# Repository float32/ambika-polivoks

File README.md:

This work is a derivative of "[Voicecard-SVF-v05](https://github.com/pichenettes/ambika/tree/master/voicecard/hardware_design/pcb)" by [Emilie Gillet](https://github.com/pichenettes), used under [CC-BY-SA 3.0](https://creativecommons.org/licenses/by-sa/3.0/).
This work is licensed under [CC-BY-SA 3.0](https://creativecommons.org/licenses/by-sa/3.0/) by [Tyler Coy](https://github.com/float32).

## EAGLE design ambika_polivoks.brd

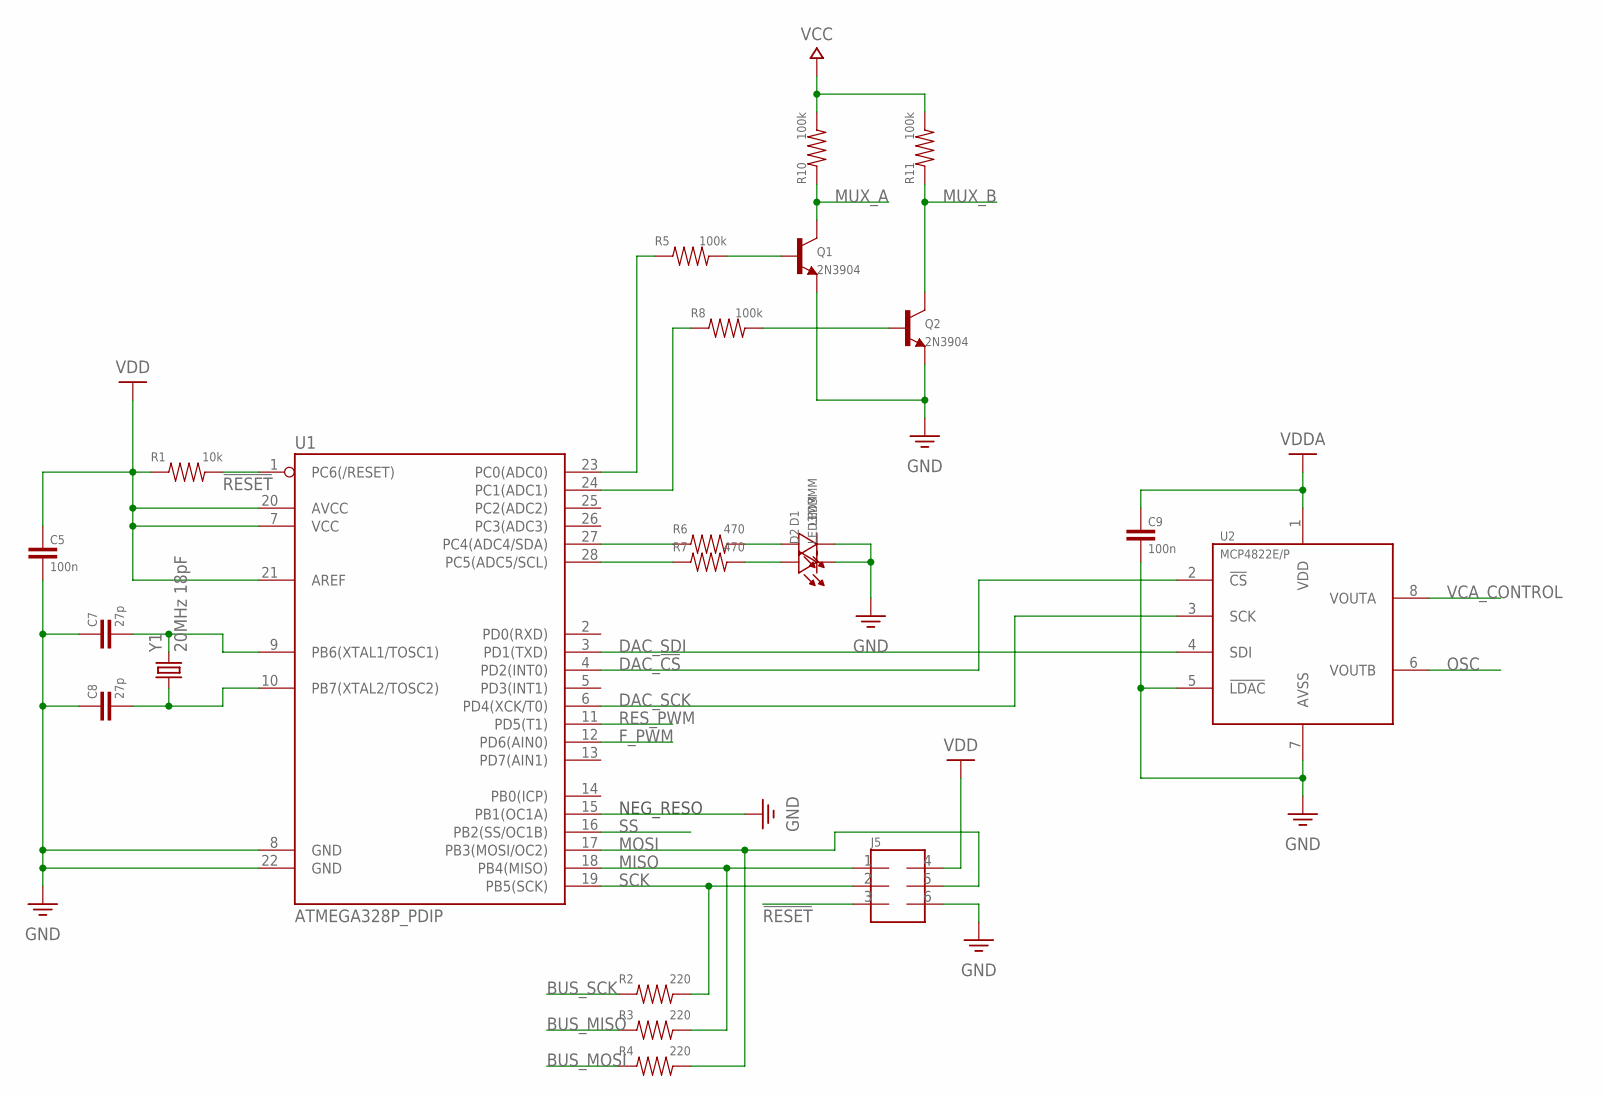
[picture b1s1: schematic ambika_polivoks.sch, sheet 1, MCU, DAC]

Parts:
C5, C9: 100n; CAP_0.1
C7, C8: 27p; CAP_0.1
D1, D2: LED3MM
J5: HEADER_2X3
Q1, Q2: 2N3904; TO-92_TRI
R1: 10k; RESISTOR_1/4W
R2, R3, R4: 220; RESISTOR_1/4W
R5, R8, R10, R11: 100k; RESISTOR_1/4W
R6, R7: 470; RESISTOR_1/4W
U1: ATMEGA328P_PDIP; DIP28
U2: MCP4822E/P; DIP8
Y1: 20MHz 18pF; HC49US

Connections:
!RESET: J5.3, R1.P$2 (2), U1.1 (PC6(/RESET))
BUS_MISO: R3.P$1 (1); also elsewhere on the board
BUS_MOSI: R4.P$1 (1); also elsewhere on the board
BUS_SCK: R2.P$1 (1); also elsewhere on the board
DAC_!CS: U1.4 (PD2(INT0)), U2.2 (!CS)
DAC_SCK: U1.6 (PD4(XCK/T0)), U2.3 (SCK)
DAC_SDI: U1.3 (PD1(TXD)), U2.4 (SDI)
F_PWM: U1.12 (PD6(AIN0)); also elsewhere on the board
GND: C5.2, C7.1, C8.1, C9.2, D1.K, D2.K, J5.6, Q1.1 (E), Q2.1 (E), U1.8 (GND), U1.15 (PB1(OC1A)), U1.22 (GND), U2.5 (!LDAC), U2.7 (AVSS); also elsewhere on the board
LED1: D2.A, R7.P$2 (2)
LED2: D1.A, R6.P$2 (2)
MISO: J5.1, R3.P$2 (2), U1.18 (PB4(MISO))
MOSI: J5.5, R4.P$2 (2), U1.17 (PB3(MOSI/OC2))
MUX_A: Q1.3 (C), R10.P$1 (1); also elsewhere on the board
MUX_B: Q2.3 (C), R11.P$1 (1); also elsewhere on the board
unnamed: C7.2, U1.9 (PB6(XTAL1/TOSC1)), Y1.2
unnamed: C8.2, U1.10 (PB7(XTAL2/TOSC2)), Y1.1
unnamed: Q1.2 (B), R5.P$2 (2)
unnamed: Q2.2 (B), R8.P$2 (2)
unnamed: R5.P$1 (1), U1.23 (PC0(ADC0))
unnamed: R8.P$1 (1), U1.24 (PC1(ADC1))
OSC: U2.6 (VOUTB); also elsewhere on the board
PC4: R6.P$1 (1), U1.27 (PC4(ADC4/SDA))
PC5: R7.P$1 (1), U1.28 (PC5(ADC5/SCL))
RES_PWM: U1.11 (PD5(T1)); also elsewhere on the board
SCK: J5.2, R2.P$2 (2), U1.19 (PB5(SCK))
SS: U1.16 (PB2(SS/OC1B)); also elsewhere on the board
VCA_CONTROL: U2.8 (VOUTA); also elsewhere on the board
VCC: R10.P$2 (2), R11.P$2 (2); also elsewhere on the board
VDD: C5.1, J5.4, R1.P$1 (1), U1.7 (VCC), U1.20 (AVCC), U1.21 (AREF); also elsewhere on the board
VDDA: C9.1, U2.1 (VDD); also elsewhere on the board

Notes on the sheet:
NEG_RESO

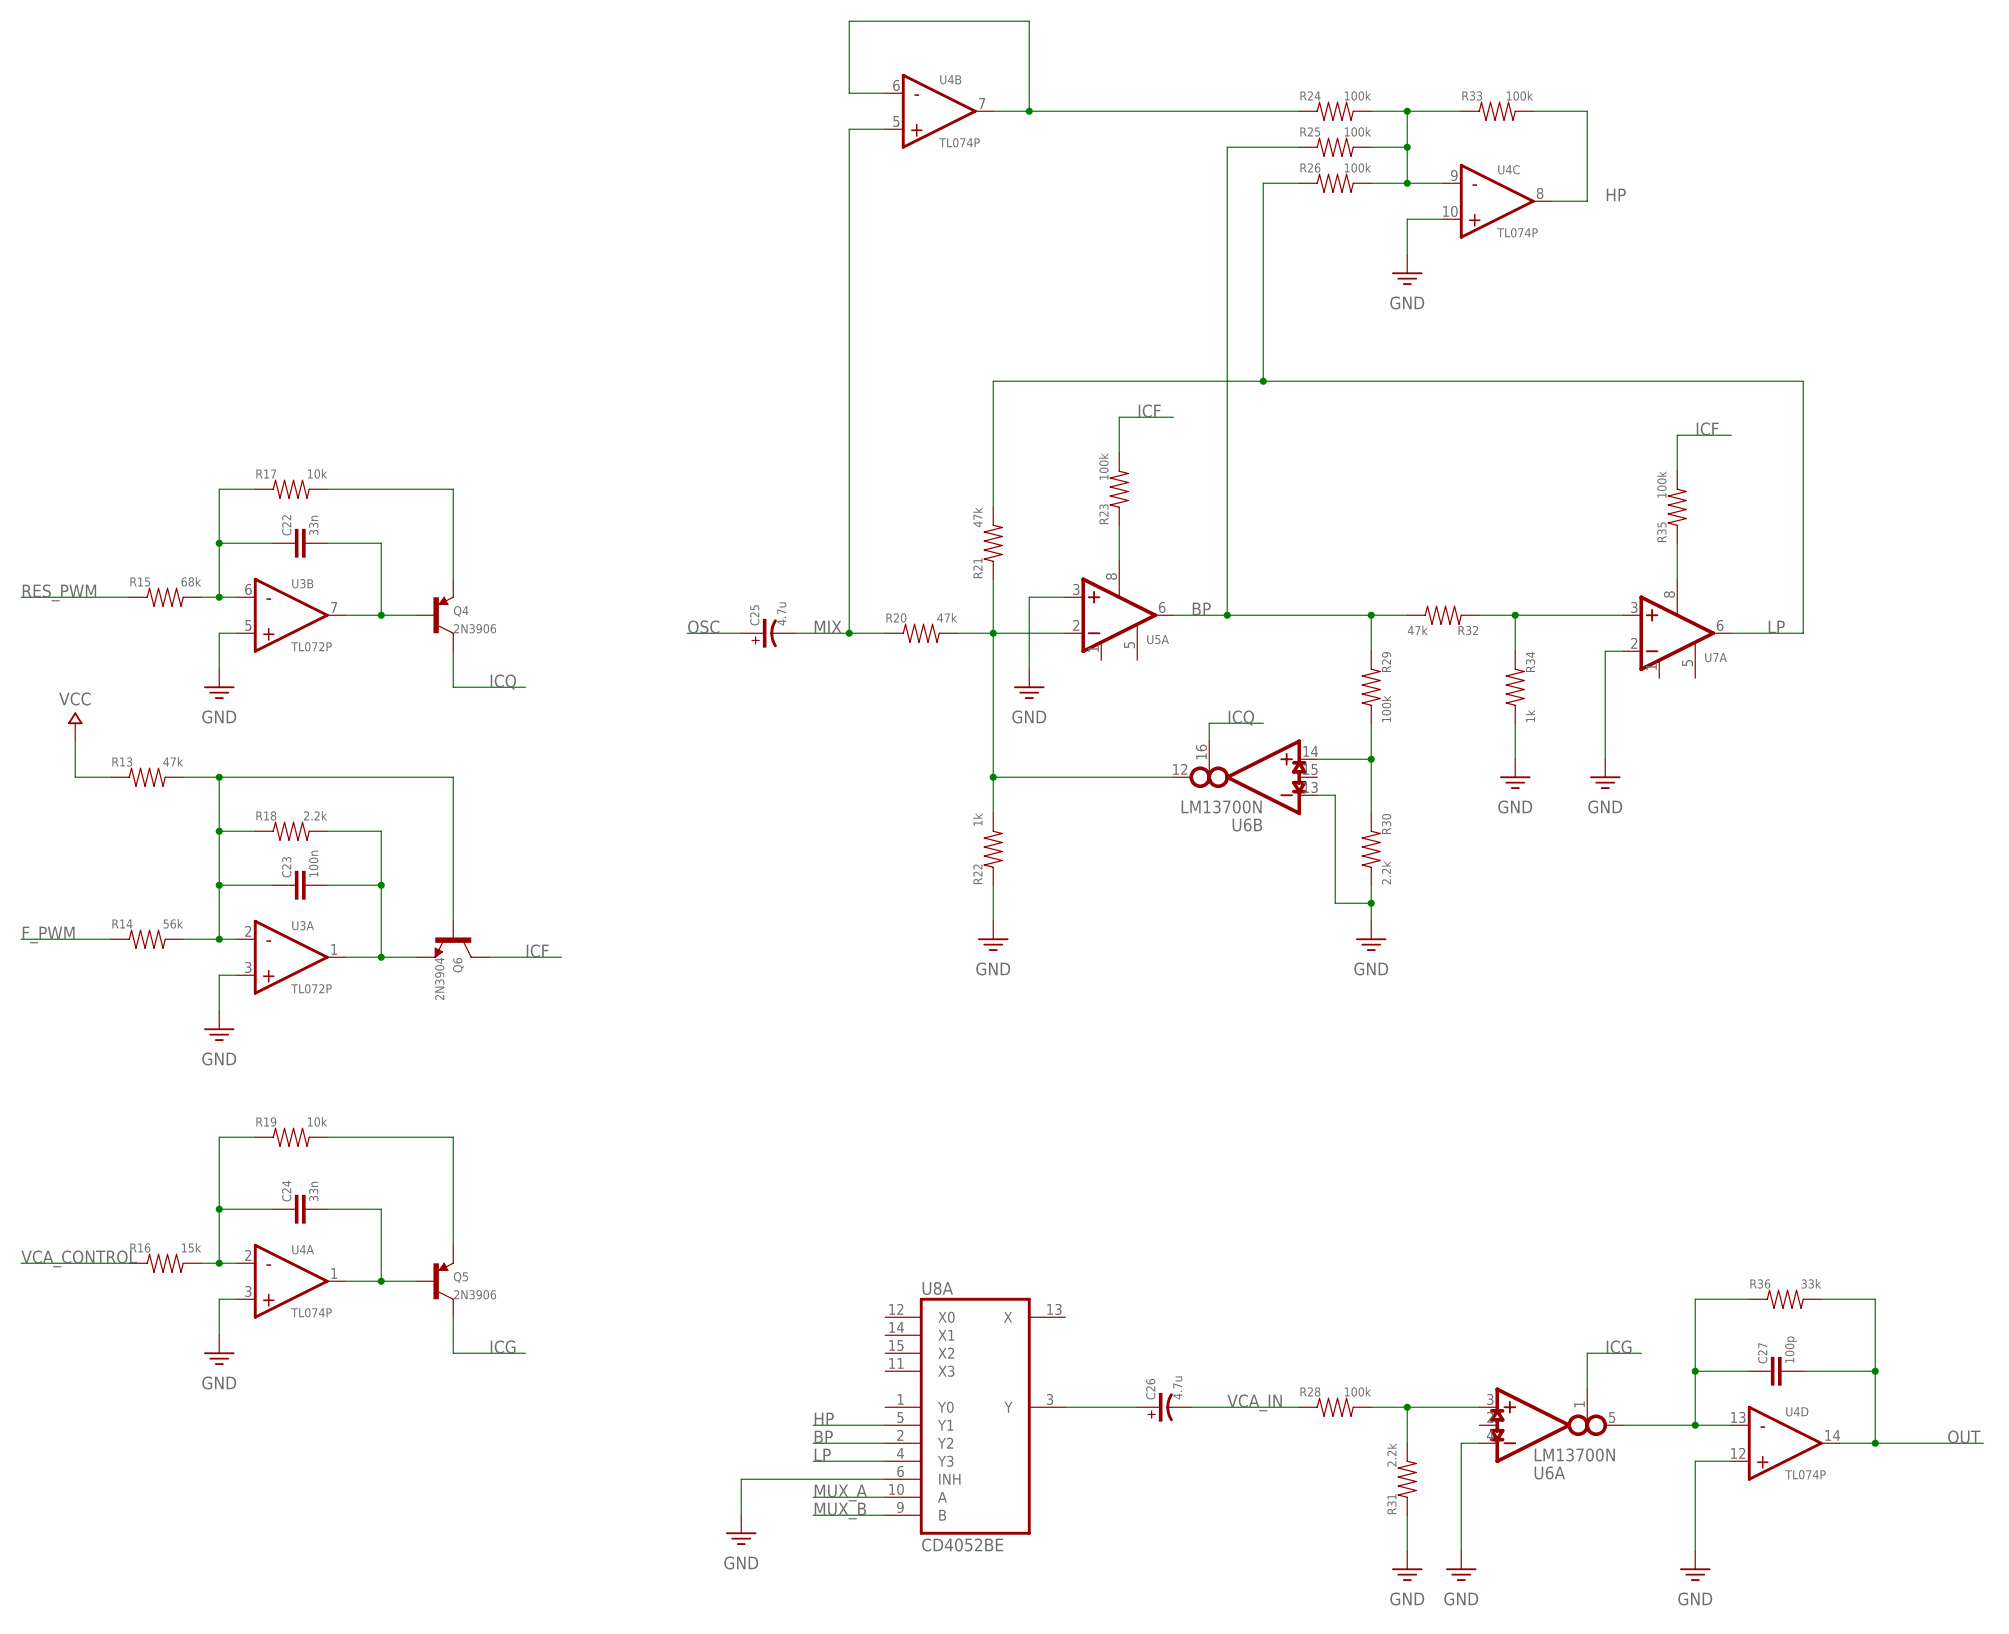
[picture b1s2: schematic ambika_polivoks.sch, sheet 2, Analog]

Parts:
C22, C24: 33n; CAP_0.1
C23: 100n; CAP_0.1
C25: 4.7u; CAP_ELEC_5MM_2MM_HORZ1
C26: 4.7u; CAP_ELEC_5MM_2MM_HORZ2
C27: 100p; CAP_0.1
Q4, Q5: 2N3906; TO-92_TRI
Q6: 2N3904; TO-92_TRI
R13, R20, R21, R32: 47k; RESISTOR_1/4W
R14: 56k; RESISTOR_1/4W
R15: 68k; RESISTOR_1/4W
R16: 15k; RESISTOR_1/4W
R17, R19: 10k; RESISTOR_1/4W
R18, R30, R31: 2.2k; RESISTOR_1/4W
R22, R34: 1k; RESISTOR_1/4W
R23, R24, R25, R26, R28, R29, R33, R35: 100k; RESISTOR_1/4W
R36: 33k; RESISTOR_1/4W
U3: TL072P; DIP8
U4: TL074P; DIP14
U5, U7: LM4250CN; DIP8
U6: LM13700N; DIP16
U8: CD4052BE; DIP16

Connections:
BP: R25.P$1 (1), R29.P$1 (1), R32.P$2 (2), U5.6 (OUTPUT), U8.2 (Y2)
F_PWM: R14.P$1 (1); also elsewhere on the board
GND: R22.P$1 (1), R30.P$2 (2), R31.P$1 (1), R34.P$2 (2), U3.3 (IN+), U3.5 (IN+), U4.3 (IN+), U4.10 (IN+), U4.12 (IN+), U5.3 (V+), U6.4 (-), U6.13 (-), U7.2 (V-), U8.6 (INH); also elsewhere on the board
HP: R33.P$2 (2), U4.8 (OUT), U8.5 (Y1)
ICF: Q6.3 (C), R23.P$2 (2), R35.P$2 (2)
ICG: Q5.3 (C), U6.1 (AMP_BIAS)
ICQ: Q4.3 (C), U6.16 (AMP_BIAS)
LP: R21.P$2 (2), R26.P$1 (1), U7.6 (OUTPUT), U8.4 (Y3)
MIX: C25.C, R20.P$1 (1), U4.5 (IN+)
MUX_A: U8.10 (A); also elsewhere on the board
MUX_B: U8.9 (B); also elsewhere on the board
unnamed: C26.A, U8.3 (Y)
unnamed: R24.P$1 (1), U4.6 (IN-), U4.7 (OUT)
unnamed: R24.P$2 (2), R25.P$2 (2), R26.P$2 (2), R33.P$1 (1), U4.9 (IN-)
unnamed: C23.2, Q6.1 (E), R18.P$2 (2), U3.1 (OUT)
unnamed: C22.2, Q4.2 (B), U3.7 (OUT)
unnamed: C22.1, R15.P$2 (2), R17.P$1 (1), U3.6 (IN-)
unnamed: Q4.1 (E), R17.P$2 (2)
unnamed: C23.1, Q6.2 (B), R13.P$2 (2), R14.P$2 (2), R18.P$1 (1), U3.2 (IN-)
unnamed: R20.P$2 (2), R21.P$1 (1), R22.P$2 (2), U5.2 (V-), U6.12 (OUTPUT)
unnamed: C24.1, R16.P$2 (2), R19.P$1 (1), U4.2 (IN-)
unnamed: C24.2, Q5.2 (B), U4.1 (OUT)
unnamed: Q5.1 (E), R19.P$2 (2)
unnamed: R23.P$1 (1), U5.8 (SET)
unnamed: R32.P$1 (1), R34.P$1 (1), U7.3 (V+)
unnamed: R29.P$2 (2), R30.P$1 (1), U6.14 (+)
unnamed: R28.P$2 (2), R31.P$2 (2), U6.3 (+)
unnamed: C27.1, R36.P$1 (1), U4.13 (IN-), U6.5 (OUTPUT)
unnamed: R35.P$1 (1), U7.8 (SET)
OSC: C25.A; also elsewhere on the board
OUT: C27.2, R36.P$2 (2), U4.14 (OUT); also elsewhere on the board
RES_PWM: R15.P$1 (1); also elsewhere on the board
VCA_CONTROL: R16.P$1 (1); also elsewhere on the board
VCA_IN: C26.C, R28.P$1 (1)
VCC: R13.P$1 (1); also elsewhere on the board

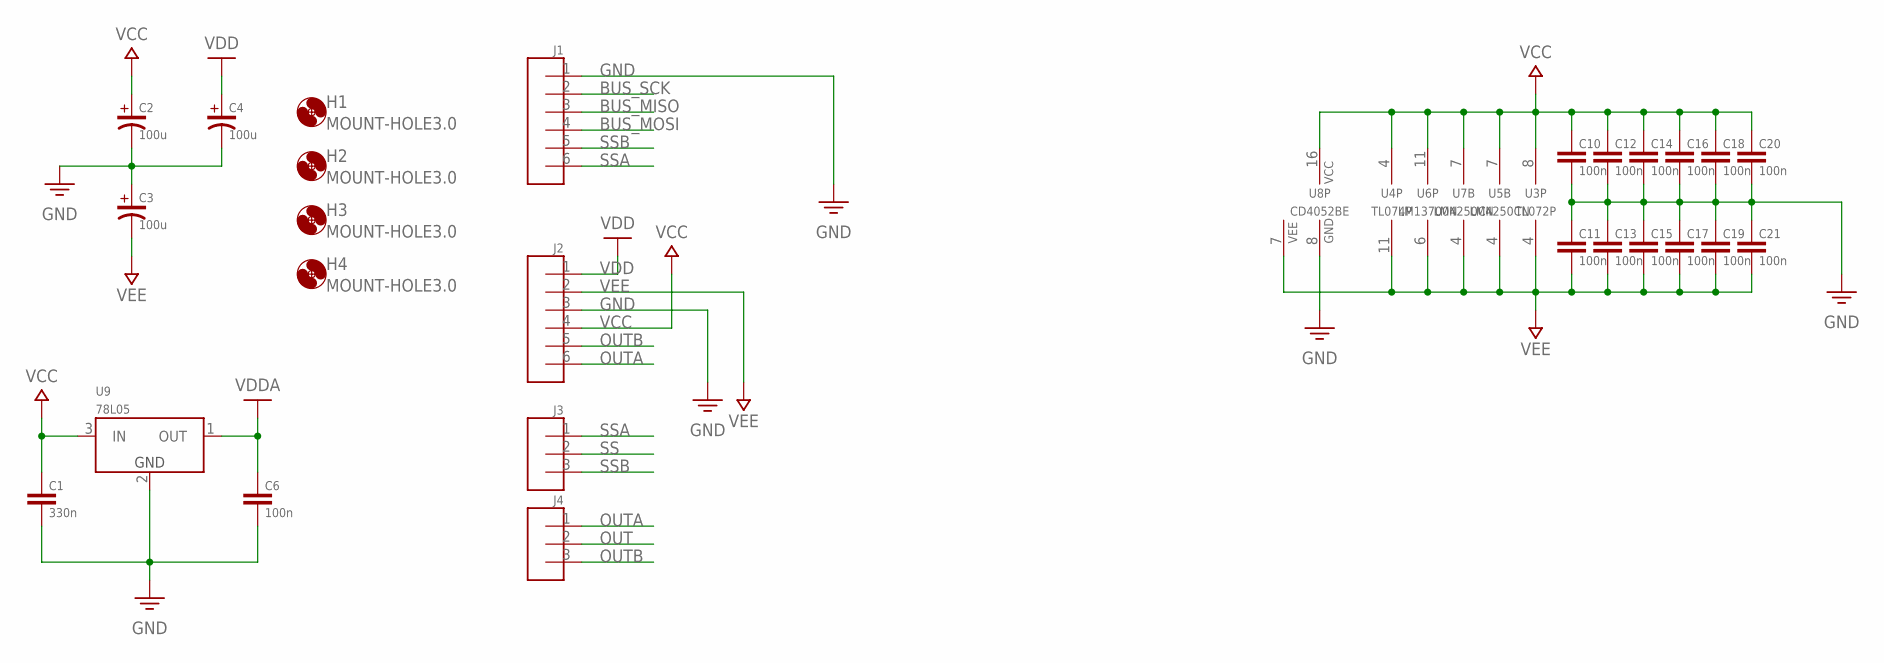
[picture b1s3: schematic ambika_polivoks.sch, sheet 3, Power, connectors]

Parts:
C1: 330n; CAP_0.1
C2, C3, C4: 100u; CAP_ELEC_6.3MM_2.5MM_HORZ2
C6, C10, C11, C12, C13, C14, C15, C16, C17, C18, C19, C20, C21: 100n; CAP_0.1
H1, H2, H3, H4: MOUNT-HOLE3.0; 3,0
J1, J2: HEADER_1X6
J3, J4: HEADER_1X3
U3: TL072P; DIP8
U4: TL074P; DIP14
U5, U7: LM4250CN; DIP8
U6: LM13700N; DIP16
U8: CD4052BE; DIP16
U9: 78L05; TO-92_TRI

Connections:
BUS_MISO: J1.3; also elsewhere on the board
BUS_MOSI: J1.4; also elsewhere on the board
BUS_SCK: J1.2; also elsewhere on the board
GND: C1.2, C2.C, C3.A, C4.C, C6.2, C10.2, C11.1, C12.2, C13.1, C14.2, C15.1, C16.2, C17.1, C18.2, C19.1, C20.2, C21.1, J1.1, J2.3, U8.8 (GND), U9.2 (GND); also elsewhere on the board
OUT: J4.2; also elsewhere on the board
OUTA: J2.6, J4.1
OUTB: J2.5, J4.3
SS: J3.2; also elsewhere on the board
SSA: J1.6, J3.1
SSB: J1.5, J3.3
VCC: C1.1, C2.A, C10.1, C12.1, C14.1, C16.1, C18.1, C20.1, J2.4, U3.8 (VCC), U4.4 (VCC), U5.7 (VCC), U6.11 (VCC), U7.7 (VCC), U8.16 (VCC), U9.3 (IN); also elsewhere on the board
VDD: C4.A, J2.1; also elsewhere on the board
VDDA: C6.1, U9.1 (OUT); also elsewhere on the board
VEE: C3.C, C11.2, C13.2, C15.2, C17.2, C19.2, C21.2, J2.2, U3.4 (VEE), U4.11 (VEE), U5.4 (VEE), U6.6 (VEE), U7.4 (VEE), U8.7 (VEE)

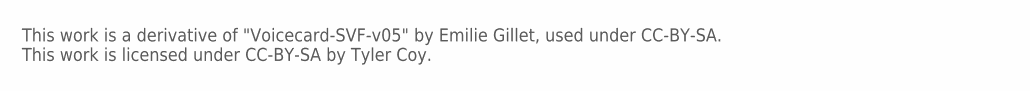
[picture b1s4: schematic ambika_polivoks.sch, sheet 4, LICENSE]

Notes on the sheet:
This work is a derivative of "Voicecard-SVF-v05" by Emilie Gillet, used under CC-BY-SA. This work is licensed under CC-BY-SA by Tyler Coy.

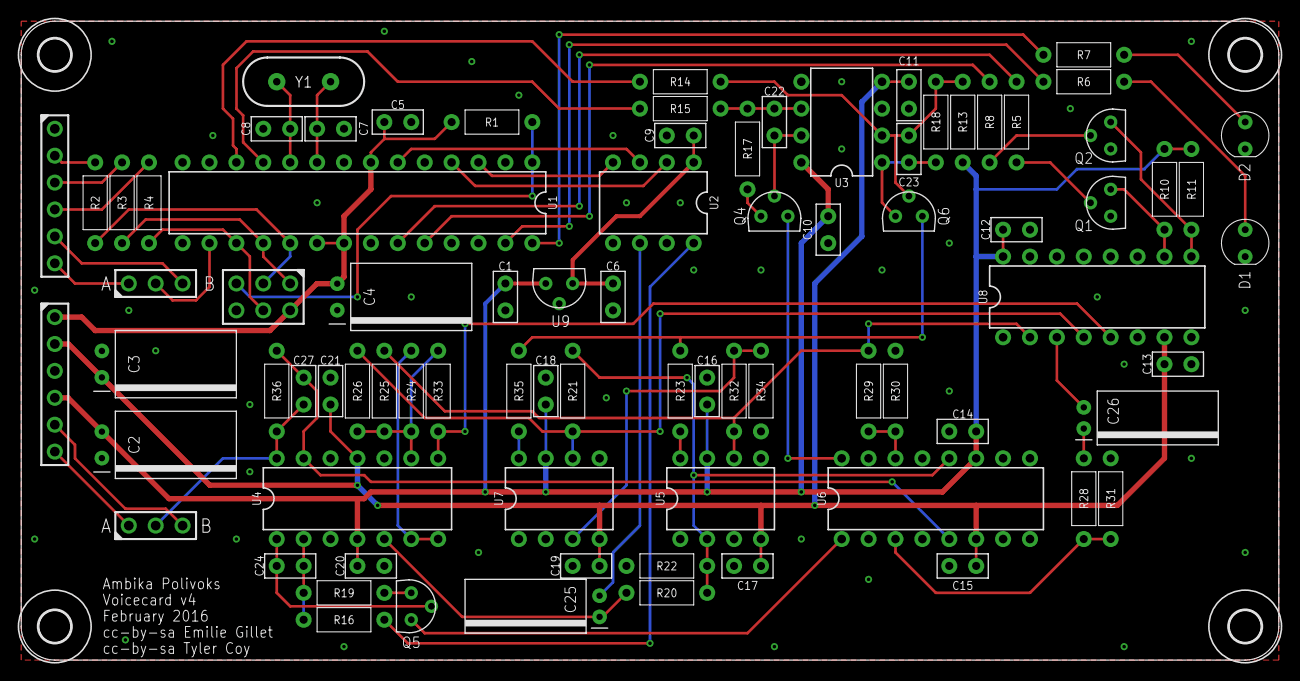
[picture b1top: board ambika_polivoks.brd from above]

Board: 2 copper layers, 118.7 x 60.3 mm, 86 parts (0 on the bottom side), 63 nets.

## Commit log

2022-01-01 Add schematic PDF

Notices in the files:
ambika_polivoks.brd:
cc-by-sa Emilie Gillet
cc-by-sa Tyler Coy
parts and their libraries:
SparkFun-FreqCtrl: Licensing: CC v3.0 Share-Alike You are welcome to use this library for commercial purposes.
